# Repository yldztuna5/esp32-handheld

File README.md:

# ESP32 Handheld

3D baskı kasalı, ESP32-S3 tabanlı, kendi arayüzü ve mini uygulamaları olan bir el konsolu.

## Hedefler
- **Güvenli batarya:** Şarjda unutulunca ısınmayan, sıcakta ve soğukta şarjı kendiliğinden durduran bir güç devresi.
- **Uzun pil ömrü:** 18650 hücre ile ~10-12 saat kullanım.
- **Ekran:** 2.8", 320x240 (bütçe nedeniyle TN; PCB ileride IPS'e geçişe uygun).
- **Kompakt yapı:** Özel PCB ile kasaya düzgünce sığan bir tasarım.
- **USB-C:** Şarj ve programlama aynı porttan.
- **Kendi yazılımı:** Launcher ve farklı oyunlar/mini uygulamalar.

## Klasörler
| Klasör | İçerik |
|---|---|
| [`docs/`](docs/) | Kararlar, güç/güvenlik tasarımı, parça listeleri |
| [`firmware/`](firmware/) | ESP32-S3 yazılımı (PlatformIO) |
| [`hardware/pcb/`](hardware/pcb/) | KiCad şema ve PCB dosyaları |
| [`hardware/case/`](hardware/case/) | 3D kasa tasarımı (STEP/STL) |

## Belgeler
- [Donanım kararları](docs/hardware.md)
- [Güç ve batarya güvenliği](docs/power-safety.md)
- [Parça listesi](docs/parts.md)
- [Pin planı](docs/pinout.md)
- [Modüllü sürüm (delikli kart)](docs/module-build.md)
- [Delikli kart yerleşimi ve bağlantı tablosu](hardware/perfboard/README.md)

## Yol haritası
- [x] Gereksinimler ve temel parça kararları
- [x] Pin planı
- [x] Tasarım incelemesi (güç, pinler, ses, mekanik) ve düzeltmeler
- [ ] Prototip parçalarını sipariş et
- [ ] Breadboard: ESP32-S3 + ekran + yön tuşu + butonlar + ses
- [ ] Firmware: launcher iskeleti ve ilk uygulama
- [x] KiCad şema (kod ile üretiliyor: `hardware/pcb/gen/`)
- [ ] Modüllü sürüm: delikli kartta montaj ([plan](docs/module-build.md))
- [ ] KiCad PCB yerleşimi (v1 taslak hazır, sipariş öncesi gözden geçirilecek)
- [ ] Kasa tasarımı (PCB ölçülerine göre)
- [ ] PCB v1 sipariş (dizgi maliyeti nedeniyle ertelendi) ve güç devresi testi (bataryasız)
- [ ] Montaj ve tam sistem testi
- [ ] PCB v2 (gerekirse)

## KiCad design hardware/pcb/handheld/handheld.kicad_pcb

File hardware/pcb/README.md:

# PCB

Kart, kodla üretilir. Tek kaynak `gen/design.py` (parçalar ve bağlantılar); şema ve kart bundan çıkar.

| Dosya | İçerik |
|---|---|
| `gen/design.py` | Devre tanımı: parçalar, pinler, LCSC kodları |
| `gen/gen_sch.py` | Şemayı üretir (`handheld/handheld.kicad_sch`) |
| `gen/gen_pcb.py`, `pcb_plan.py`, `pcb_route.py` | Kart yerleşimi ve yollar (`handheld/handheld.kicad_pcb`) |
| `gen/check_netlist.py`, `gen/check_pcb.py` | Şema ve kartın `design.py` ile birebir uyduğunu denetler |
| `gen/fab.py` | Üretim dosyaları (`handheld/fab/`) |
| `handheld/handheld-schematic.pdf` | Şemanın PDF'i |
| `handheld/render-top.png`, `render-bottom.png` | Kartın ön ve arka görüntüsü |
| `handheld/fab/gerbers.zip`, `bom-jlcpcb.csv`, `cpl-jlcpcb.csv` | Fiyat teklifi ve sipariş için yüklenecek dosyalar |

Yeniden üretmek için `gen/` içinde `run.ps1` (KiCad 9 gerekir), sonra `check_pcb.py` ve `fab.py`.

## Durum (v1.1 taslak)
- 90 x 100 mm, 2 katman. Bütün SMD parçalar arka yüzde (tek yüz dizgi); ön yüzde ekran başlıkları ve butonlar.
- Ana güç yolları en az 0,6 mm (batarya hattı 1,0 mm); sadece çip pinlerine girişte 1-2 mm'lik ince boyunlar var.
- ERC: 0 hata. DRC: 0 hata, 0 bağlanmamış uç, şema ile uyumlu.
- **Sipariş öncesi yapılacaklar:**
  - JLCPCB dizgi dosyasındaki parça yönlerini (rotation) önizlemede tek tek kontrol etmek.
  - Gerber'leri bir görüntüleyicide açıp bakmak.
  - Ekran modülü gelince delik ve başlık konumlarını cetvelle doğrulamak.
  - Pinleri breadboard'da denemek.

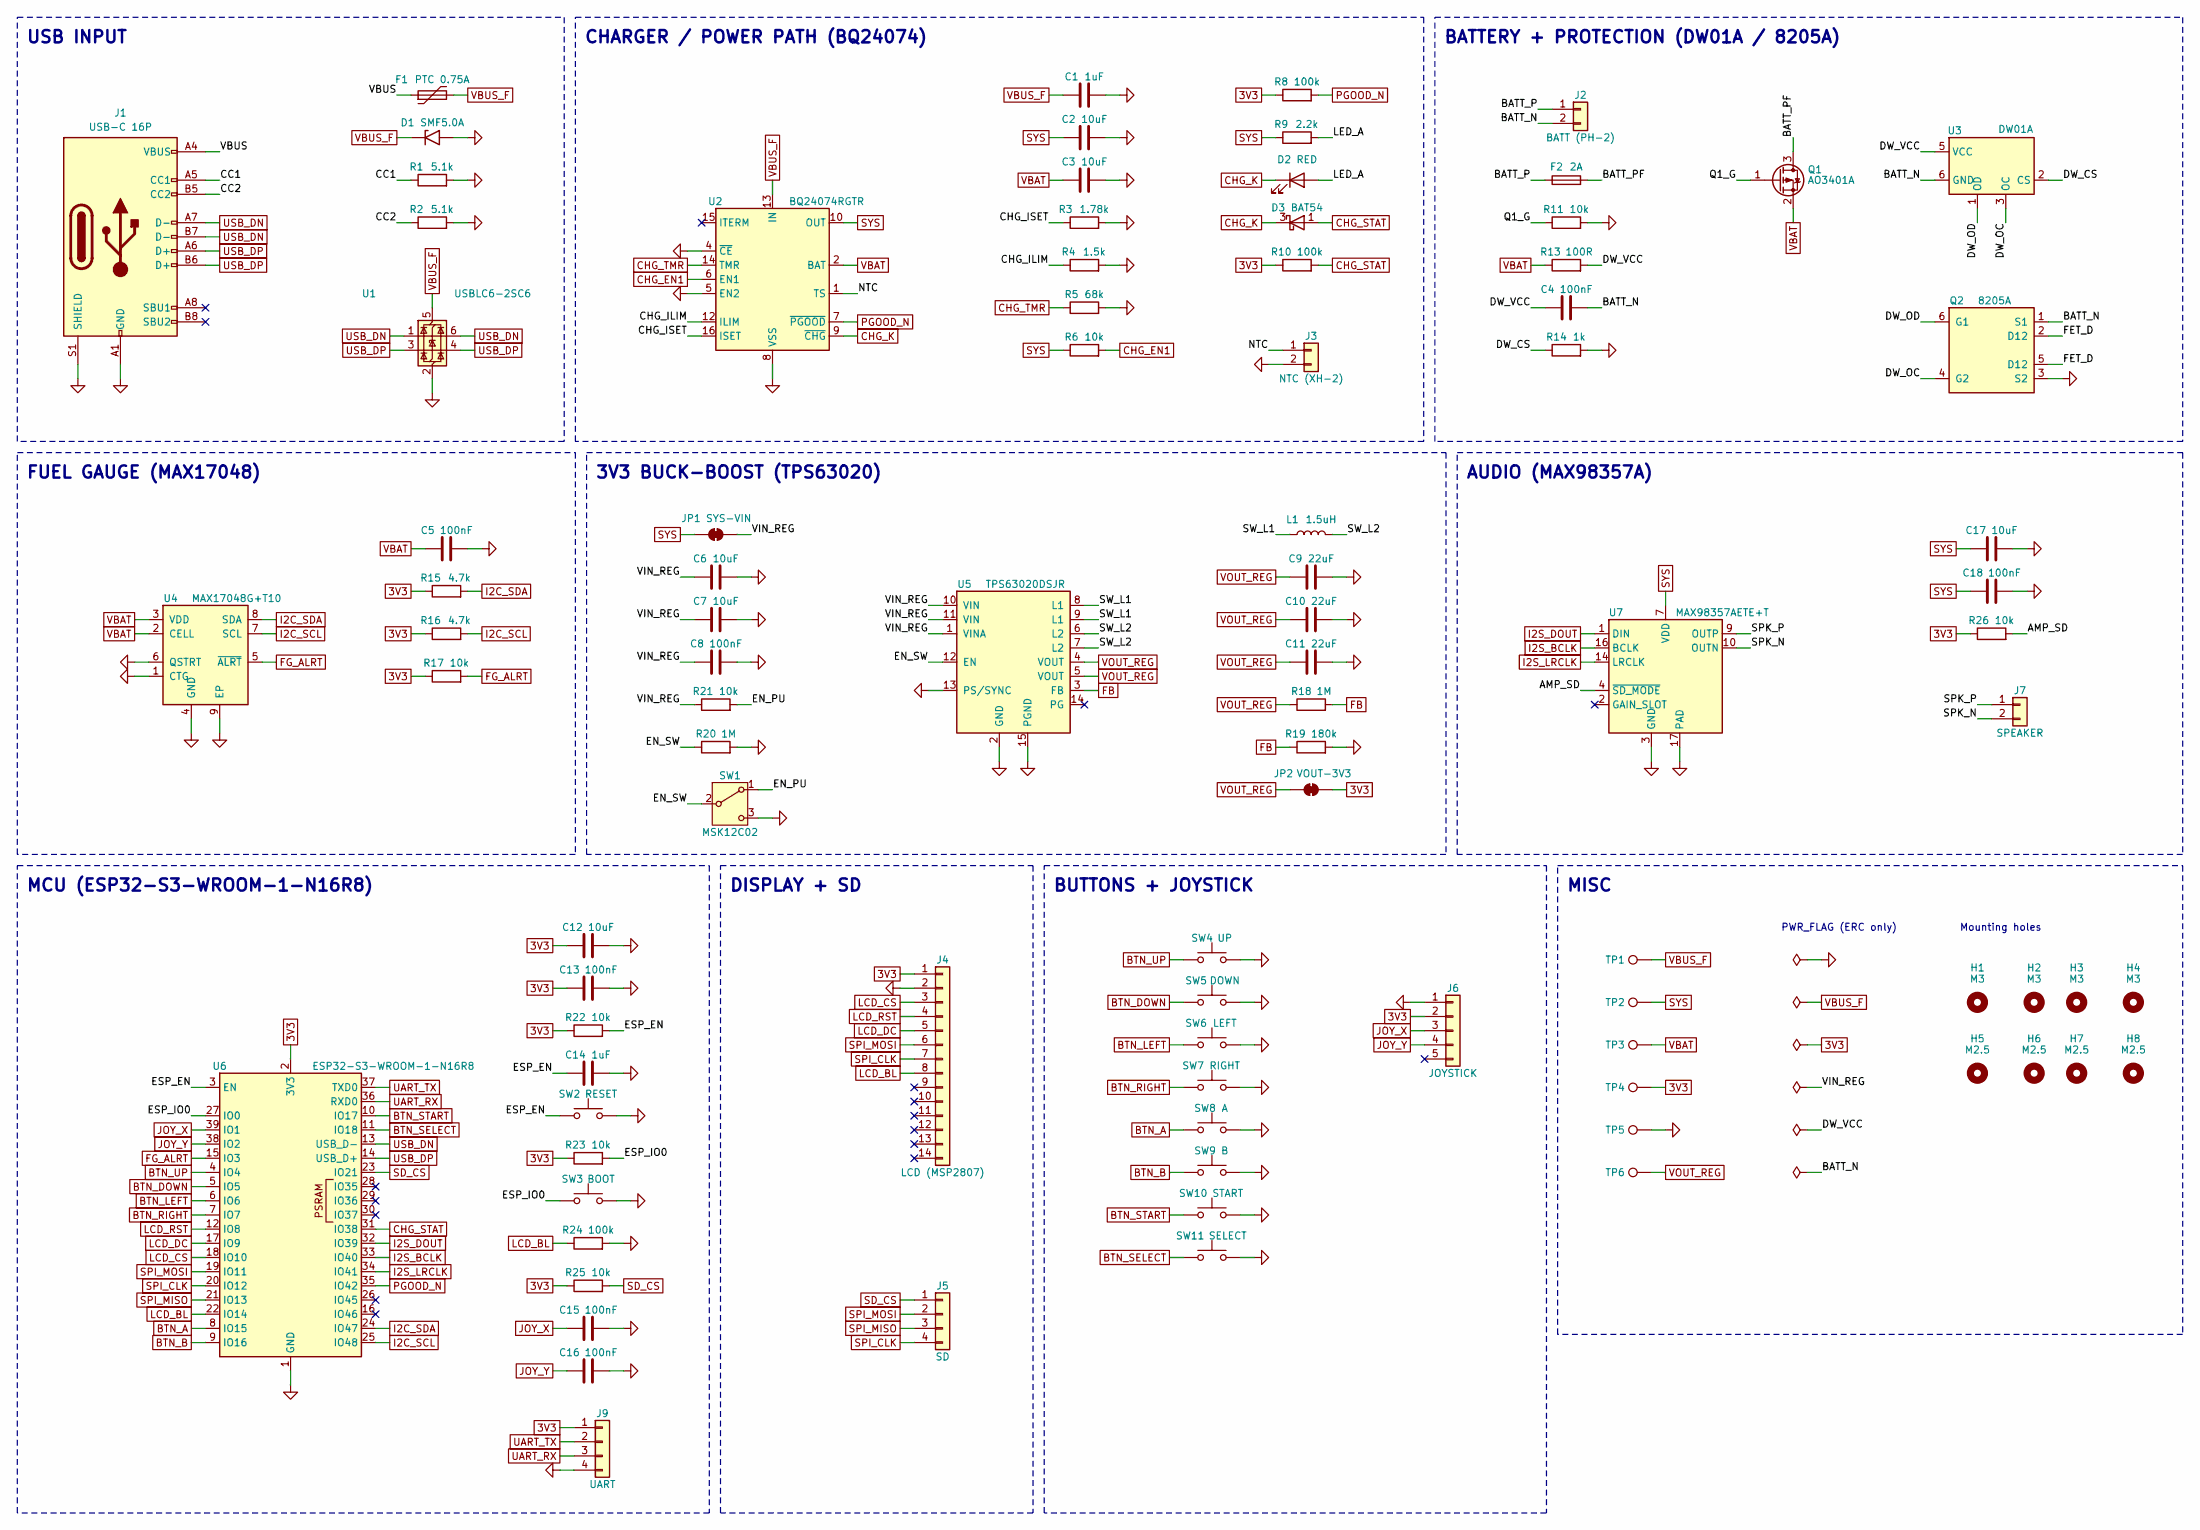
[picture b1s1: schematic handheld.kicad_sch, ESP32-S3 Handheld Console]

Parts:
C1, C14: 1uF; C_0603_1608Metric; LCSC C15849
C2, C3, C6, C7, C12, C17: 10uF; C_0603_1608Metric; LCSC C96446
C4, C5, C8, C13, C15, C16, C18: 100nF; C_0603_1608Metric; LCSC C14663
C9, C10, C11: 22uF; C_0805_2012Metric; LCSC C45783
D1: SMF5.0A; D_SOD-123F; LCSC C193402
D2: RED; LED_0603_1608Metric; LCSC C2286
D3: BAT54; SOT-23; LCSC C8590
F1: PTC 0.75A; Fuse_1206_3216Metric; LCSC C20987
F2: 2A; Fuse_1206_3216Metric; LCSC C3105
H1, H2, H3, H4: M3; MountingHole_3.2mm_M3
H5, H6, H7, H8: M2.5; MountingHole_2.7mm_M2.5
J1: USB-C 16P; USB_C_Receptacle_HRO_TYPE-C-31-M-12; LCSC C165948
J2: BATT (PH-2); JST_PH_S2B-PH-K_1x02_P2.00mm_Horizontal
J3: NTC (XH-2); JST_XH_B2B-XH-A_1x02_P2.50mm_Vertical
J4: LCD (MSP2807); PinSocket_1x14_P2.54mm_Vertical
J5: SD; PinSocket_1x04_P2.54mm_Vertical
J6: JOYSTICK; PinHeader_1x05_P2.54mm_Vertical
J7: SPEAKER; PinHeader_1x02_P2.54mm_Vertical
J9: UART; PinHeader_1x04_P2.54mm_Vertical
JP1: SYS-VIN; SolderJumper-2_P1.3mm_Bridged_RoundedPad1.0x1.5mm
JP2: VOUT-3V3; SolderJumper-2_P1.3mm_Bridged_RoundedPad1.0x1.5mm
L1: 1.5uH; L_Changjiang_FNR4020S; LCSC C167824
Q1: AO3401A; SOT-23; LCSC C15127
Q2: 8205A; SOT-23-6; LCSC C351449
R1, R2: 5.1k; R_0603_1608Metric; LCSC C23186
R3: 1.78k; R_0603_1608Metric; LCSC C13118
R4: 1.5k; R_0603_1608Metric; LCSC C22843
R5: 68k; R_0603_1608Metric; LCSC C23231
R6, R11, R17, R21, R22, R23, R25, R26: 10k; R_0603_1608Metric; LCSC C25804
R8, R10, R24: 100k; R_0603_1608Metric; LCSC C25803
R9: 2.2k; R_0603_1608Metric; LCSC C4190
R13: 100R; R_0603_1608Metric; LCSC C22775
R14: 1k; R_0603_1608Metric; LCSC C21190
R15, R16: 4.7k; R_0603_1608Metric; LCSC C23162
R18, R20: 1M; R_0603_1608Metric; LCSC C22935
R19: 180k; R_0603_1608Metric; LCSC C22827
SW1: MSK12C02; SW_SPDT_Shouhan_MSK12C02; LCSC C431540
SW2: RESET; SW_Push_1P1T_XKB_TS-1187A; LCSC C318884
SW3: BOOT; SW_Push_1P1T_XKB_TS-1187A; LCSC C318884
SW4: UP; SW_PUSH_6mm
SW5: DOWN; SW_PUSH_6mm
SW6: LEFT; SW_PUSH_6mm
SW7: RIGHT; SW_PUSH_6mm
SW8: A; SW_PUSH_6mm
SW9: B; SW_PUSH_6mm
SW10: START; SW_PUSH_6mm
SW11: SELECT; SW_PUSH_6mm
TP1: VBUS_F; TestPoint_Pad_D1.5mm
TP2: SYS; TestPoint_Pad_D1.5mm
TP3: VBAT; TestPoint_Pad_D1.5mm
TP4: 3V3; TestPoint_Pad_D1.5mm
TP5: GND; TestPoint_Pad_D1.5mm
TP6: VOUT_REG; TestPoint_Pad_D1.5mm
U1: USBLC6-2SC6; SOT-23-6; LCSC C7519
U2: BQ24074RGTR; VQFN-16-1EP_3x3mm_P0.5mm_EP1.6x1.6mm; LCSC C54313
U3: DW01A; SOT-23-6; LCSC C351410
U4: MAX17048G+T10; TDFN-8-1EP_2x2mm_P0.5mm_EP0.8x1.2mm; LCSC C2682616
U5: TPS63020DSJR; TPS63020_DSJ; LCSC C15483
U6: ESP32-S3-WROOM-1-N16R8; ESP32-S3-WROOM-1; LCSC C2913202
U7: MAX98357AETE+T; TQFN-16-1EP_3x3mm_P0.5mm_EP1.23x1.23mm; LCSC C910544

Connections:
3V3: C12.1, C13.1, J4.1, J6.2, J9.1, JP2.2 (B), R8.1, R10.1, R15.1, R16.1, R17.1, R22.1, R23.1, R25.1, R26.1, TP4.1, U6.2 (3V3)
/AMP_SD: R26.2, U7.4 (~SD_MODE)
/BATT_N: C4.2, J2.2, Q2.1 (S1), U3.6 (GND)
/BATT_P: F2.1, J2.1
/BATT_PF: F2.2, Q1.3 (D)
/CC1: J1.A5 (CC1), R1.1
/CC2: J1.B5 (CC2), R2.1
/CHG_ILIM: R4.1, U2.12 (ILIM)
/CHG_ISET: R3.1, U2.16 (ISET)
/DW_CS: R14.1, U3.2 (CS)
/DW_OC: Q2.4 (G2), U3.3 (OC)
/DW_OD: Q2.6 (G1), U3.1 (OD)
/DW_VCC: C4.1, R13.2, U3.5 (VCC)
/EN_PU: R21.2, SW1.1 (A)
/EN_SW: R20.1, SW1.2 (B), U5.12 (EN)
/ESP_EN: C14.1, R22.2, SW2.1, U6.3 (EN)
/ESP_IO0: R23.2, SW3.1, U6.27 (IO0)
/FET_D: Q2.2 (D12), Q2.5 (D12)
/LED_A: D2.2 (A), R9.2
/NTC: J3.1, U2.1 (TS)
/Q1_G: Q1.1 (G), R11.1
/SPK_N: J7.2, U7.10 (OUTN)
/SPK_P: J7.1, U7.9 (OUTP)
/SW_L1: L1.1, U5.8 (L1), U5.9 (L1)
/SW_L2: L1.2, U5.6 (L2), U5.7 (L2)
/VBUS: F1.1, J1.A4 (VBUS), J1.A9 (VBUS), J1.B4 (VBUS), J1.B9 (VBUS)
/VIN_REG: C6.1, C7.1, C8.1, JP1.2 (B), R21.1, U5.1 (VINA), U5.10 (VIN), U5.11 (VIN)
BTN_A: SW8.1, U6.8 (IO15)
BTN_B: SW9.1, U6.9 (IO16)
BTN_DOWN: SW5.1, U6.5 (IO5)
BTN_LEFT: SW6.1, U6.6 (IO6)
BTN_RIGHT: SW7.1, U6.7 (IO7)
BTN_SELECT: SW11.1, U6.11 (IO18)
BTN_START: SW10.1, U6.10 (IO17)
BTN_UP: SW4.1, U6.4 (IO4)
CHG_EN1: R6.2, U2.6 (EN1)
CHG_K: D2.1 (K), D3.3 (K), U2.9 (~CHG)
CHG_STAT: D3.1 (A), R10.2, U6.31 (IO38)
CHG_TMR: R5.1, U2.14 (TMR)
FB: R18.2, R19.1, U5.3 (FB)
FG_ALRT: R17.2, U4.5 (~ALRT), U6.15 (IO3)
GND: C1.2, C2.2, C3.2, C5.2, C6.2, C7.2, C8.2, C9.2, C10.2, C11.2, C12.2, C13.2, C14.2, C15.2, C16.2, C17.2, C18.2, D1.2 (A2), J1.A1 (GND), J1.A12 (GND), J1.B1 (GND), J1.B12 (GND), J1.S1 (SHIELD), J3.2, J4.2, J6.1, J9.4, Q2.3 (S2), R1.2, R2.2, R3.2, R4.2, R5.2, R11.2, R14.2, R19.2, R20.2, R24.2, SW1.3 (C), SW2.2, SW3.2, SW4.2, SW5.2, SW6.2, SW7.2, SW8.2, SW9.2, SW10.2, SW11.2, TP5.1, U1.2 (GND), U2.4 (~CE), U2.5 (EN2), U2.8 (VSS), U2.17 (VSS), U4.1 (CTG), U4.4 (GND), U4.6 (QSTRT), U4.9 (EP), U5.2 (GND), U5.13 (PS/SYNC), U5.15 (PGND), U6.1 (GND), U6.40 (GND), U6.41 (GND), U7.3 (GND), U7.11 (GND), U7.15 (GND), U7.17 (PAD)
I2C_SCL: R16.2, U4.7 (SCL), U6.25 (IO48)
I2C_SDA: R15.2, U4.8 (SDA), U6.24 (IO47)
I2S_BCLK: U6.33 (IO40), U7.16 (BCLK)
I2S_DOUT: U6.32 (IO39), U7.1 (DIN)
I2S_LRCLK: U6.34 (IO41), U7.14 (LRCLK)
JOY_X: C15.1, J6.3, U6.39 (IO1)
JOY_Y: C16.1, J6.4, U6.38 (IO2)
LCD_BL: J4.8, R24.1, U6.22 (IO14)
LCD_CS: J4.3, U6.18 (IO10)
LCD_DC: J4.5, U6.17 (IO9)
LCD_RST: J4.4, U6.12 (IO8)
PGOOD_N: R8.2, U2.7 (~PGOOD), U6.35 (IO42)
SD_CS: J5.1, R25.2, U6.23 (IO21)
SPI_CLK: J4.7, J5.4, U6.20 (IO12)
SPI_MISO: J5.3, U6.21 (IO13)
SPI_MOSI: J4.6, J5.2, U6.19 (IO11)
SYS: C2.1, C17.1, C18.1, JP1.1 (A), R6.1, R9.1, TP2.1, U2.10 (OUT), U2.11 (OUT), U7.7 (VDD), U7.8 (VDD)
UART_RX: J9.3, U6.36 (RXD0)
UART_TX: J9.2, U6.37 (TXD0)
USB_DN: J1.A7 (D-), J1.B7 (D-), U1.1 (I/O1), U1.6 (I/O1), U6.13 (USB_D-)
USB_DP: J1.A6 (D+), J1.B6 (D+), U1.3 (I/O2), U1.4 (I/O2), U6.14 (USB_D+)
VBAT: C3.1, C5.1, Q1.2 (S), R13.1, TP3.1, U2.2 (BAT), U2.3 (BAT), U4.2 (CELL), U4.3 (VDD)
VBUS_F: C1.1, D1.1 (A1), F1.2, TP1.1, U1.5 (VBUS), U2.13 (IN)
VOUT_REG: C9.1, C10.1, C11.1, JP2.1 (A), R18.1, TP6.1, U5.4 (VOUT), U5.5 (VOUT)

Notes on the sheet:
USB INPUT
CHARGER / POWER PATH (BQ24074)
BATTERY + PROTECTION (DW01A / 8205A)
FUEL GAUGE (MAX17048)
3V3 BUCK-BOOST (TPS63020)
AUDIO (MAX98357A)
MCU (ESP32-S3-WROOM-1-N16R8)
DISPLAY + SD
BUTTONS + JOYSTICK
MISC
PWR_FLAG (ERC only)
Mounting holes

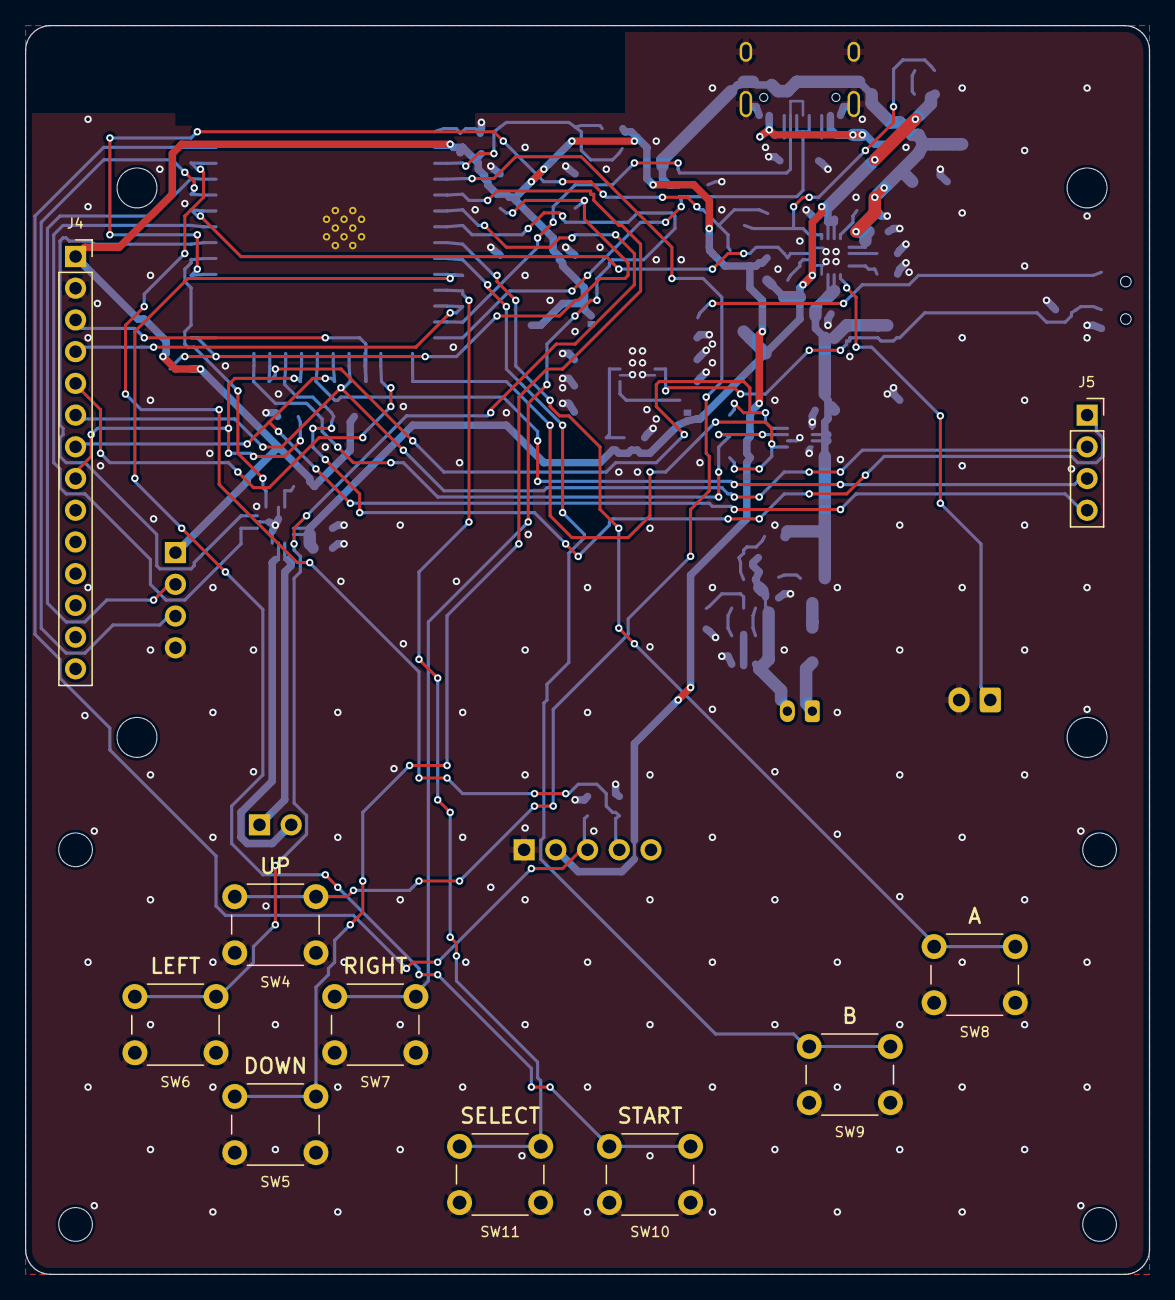
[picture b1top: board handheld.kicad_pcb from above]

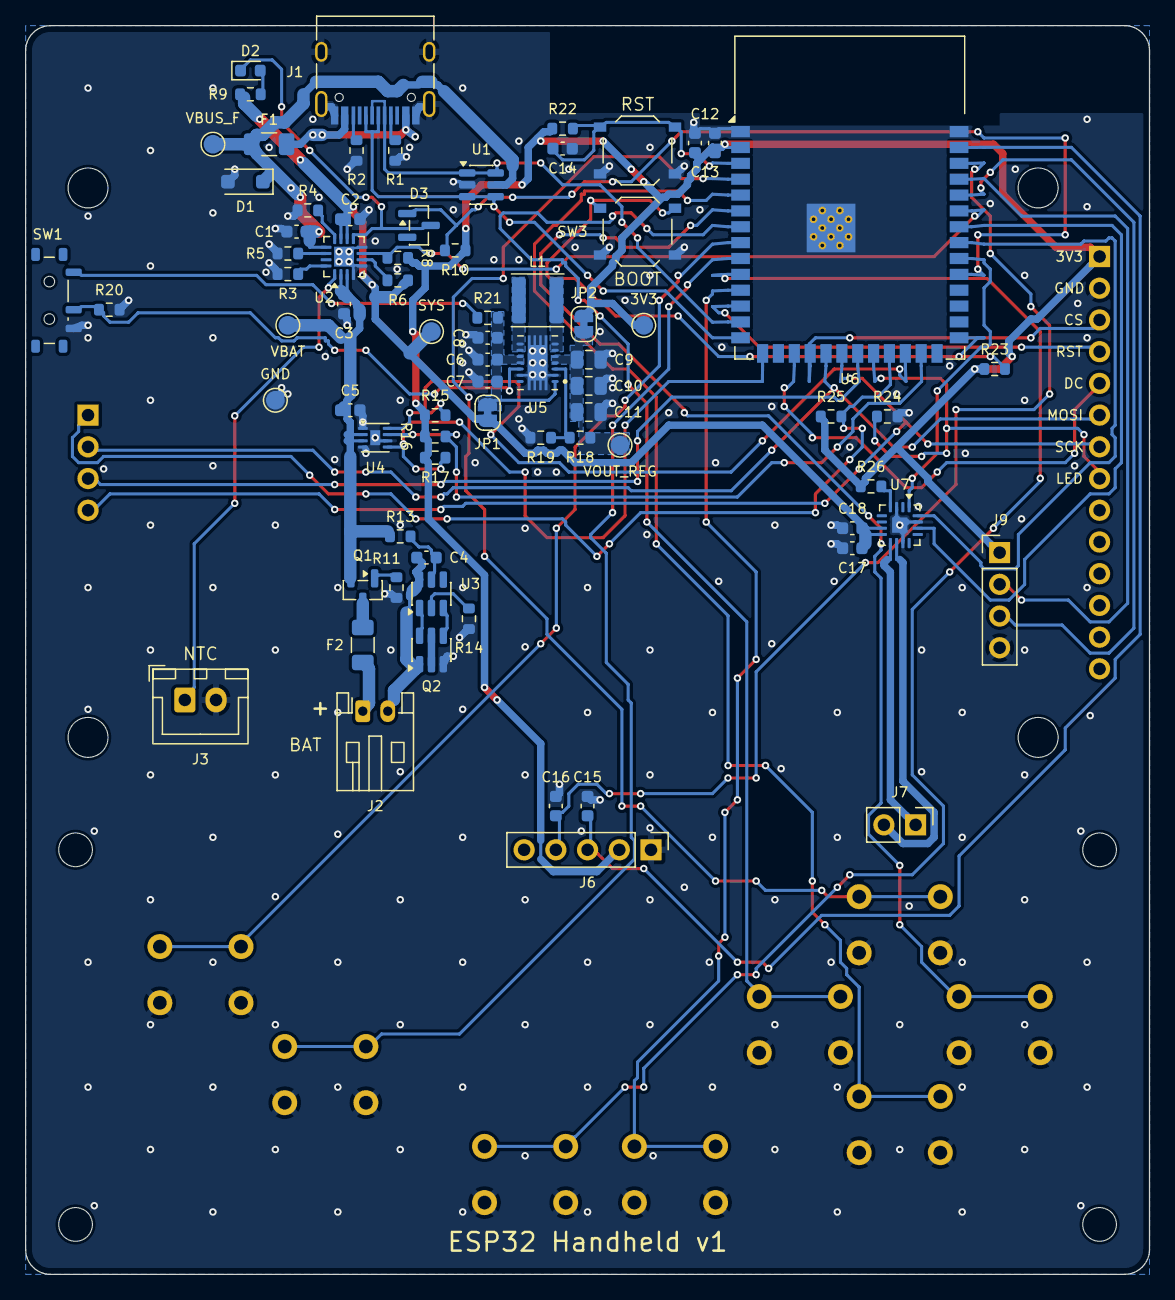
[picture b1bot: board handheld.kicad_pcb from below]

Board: 2 copper layers, 90.0 x 100.0 mm, 92 parts (74 on the bottom side), 66 nets.

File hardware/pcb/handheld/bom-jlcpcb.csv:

Comment,Designator,Footprint,LCSC Part #
1uF,"C1,C14",C_0603_1608Metric,C15849
10uF,"C2,C3,C6,C7,C12,C17",C_0603_1608Metric,C96446
100nF,"C4,C5,C8,C13,C15,C16,C18",C_0603_1608Metric,C14663
22uF,"C9,C10,C11",C_0805_2012Metric,C45783
SMF5.0A,D1,D_SOD-123F,C193402
RED,D2,LED_0603_1608Metric,C2286
BAT54,D3,SOT-23,C8590
PTC 0.75A,F1,Fuse_1206_3216Metric,C20987
2A,F2,Fuse_1206_3216Metric,C3105
USB-C 16P,J1,USB_C_Receptacle_HRO_TYPE-C-31-M-12,C165948
1.5uH,L1,L_Changjiang_FNR4020S,C167824
AO3401A,Q1,SOT-23,C15127
8205A,Q2,SOT-23-6,C351449
5.1k,"R1,R2",R_0603_1608Metric,C23186
1.78k,R3,R_0603_1608Metric,C13118
1.5k,R4,R_0603_1608Metric,C22843
68k,R5,R_0603_1608Metric,C23231
10k,"R6,R11,R17,R21,R22,R23,R25,R26",R_0603_1608Metric,C25804
100k,"R8,R10,R24",R_0603_1608Metric,C25803
2.2k,R9,R_0603_1608Metric,C4190
100R,R13,R_0603_1608Metric,C22775
1k,R14,R_0603_1608Metric,C21190
4.7k,"R15,R16",R_0603_1608Metric,C23162
1M,"R18,R20",R_0603_1608Metric,C22935
180k,R19,R_0603_1608Metric,C22827
MSK12C02,SW1,SW_SPDT_Shouhan_MSK12C02,C431540
RESET,SW2,SW_Push_1P1T_XKB_TS-1187A,C318884
BOOT,SW3,SW_Push_1P1T_XKB_TS-1187A,C318884
USBLC6-2SC6,U1,SOT-23-6,C7519
BQ24074RGTR,U2,VQFN-16-1EP_3x3mm_P0.5mm_EP1.6x1.6mm,C54313
DW01A,U3,SOT-23-6,C351410
MAX17048G+T10,U4,TDFN-8-1EP_2x2mm_P0.5mm_EP0.8x1.2mm,C2682616
TPS63020DSJR,U5,TPS63020_DSJ,C15483
ESP32-S3-WROOM-1-N16R8,U6,ESP32-S3-WROOM-1,C2913202
MAX98357AETE+T,U7,TQFN-16-1EP_3x3mm_P0.5mm_EP1.23x1.23mm,C910544

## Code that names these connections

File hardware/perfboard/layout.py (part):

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# Source-of-truth GPIO table encoded from docs/pinout.md and docs/module-build.md
# ---------------------------------------------------------------------------
PINOUT_GPIO_MAP: Dict[str, str] = {
    "GPIO10": "LCD_CS",
    "GPIO11": "SPI_MOSI",   # LCD_MOSI + SD_MOSI shared FSPI MOSI
    "GPIO12": "SPI_SCK",    # LCD_CLK + SD_CLK shared FSPI SCK
    "GPIO9": "LCD_DC",
    "GPIO8": "LCD_RST",
    "GPIO14": "LCD_BL",
    "GPIO13": "SPI_MISO",   # LCD_MISO + SD_MISO shared FSPI MISO
    "GPIO21": "SD_CS",
    "GPIO4": "DPAD_UP",
    "GPIO5": "DPAD_DOWN",
    "GPIO6": "DPAD_LEFT",
    "GPIO7": "DPAD_RIGHT",
    "GPIO15": "BTN_A",
    "GPIO16": "BTN_B",
    "GPIO17": "BTN_START",
    "GPIO18": "BTN_SELECT",
    "GPIO1": "JOY_X",
    "GPIO2": "JOY_Y",
    "GPIO39": "AUDIO_OUT",
    "GPIO3": "BAT_ADC",     # Battery voltage divider on perfboard (docs/module-build.md)
}
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    "TX(43)",   # UART0 TX debug
    "RX(44)",   # UART0 RX debug
    "GPIO42",   # PCB-only PGOOD
    "GPIO41",   # PCB-only I2S_LRCLK
    "GPIO40",   # PCB-only I2S_BCLK
    "GPIO38",   # PCB-only CHG_STAT
    "GPIO37",   # Octal PSRAM (unavailable on N16R8)
    "GPIO36",   # Octal PSRAM (unavailable on N16R8)
    "GPIO35",   # Octal PSRAM (unavailable on N16R8)
    "GPIO0",    # Strapping / onboard BOOT button
    "GPIO45",   # Strapping VDD_SPI (must NEVER be pulled high)
    "GPIO48",   # PCB-only I2C_SCL / onboard RGB LED
    "GPIO47",   # PCB-only I2C_SDA
    "GPIO20",   # USB D+
    "GPIO19",   # USB D-
}
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            description="Ekran Üst 1x4 SD Header Uçan Kablo Padleri (SD_CS, MOSI, MISO, SCK)",
            body=(9, 26, 10, 27),
            pins=[
                Pin("SD_CS", 9, 26, nc=False),
                Pin("SD_MOSI", 10, 26, nc=False),
                Pin("SD_MISO", 9, 27, nc=False),
                Pin("SD_SCK", 10, 27, nc=False),
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    lines.append("")
    lines.append("| Ekran Üst SD Pini | Hat Adı (Net) | `ARKA` Kart Lehim Padi (`PAD_SD`) | ESP32 Pini | Ek Eleman / Not |")
    lines.append("|---|---|---|---|---|")
    lines.append("| `SD_CS` | `SD_CS` | `PAD_SD.SD_CS` @ ARKA (9,26) | `GPIO21` (`J3_18_21` @ 10,19) | `R_SD` (10k pull-up -> `3V3`) |")
    lines.append("| `SD_MOSI` | `SPI_MOSI` | `PAD_SD.SD_MOSI` @ ARKA (10,26) | `GPIO11` (`J1_17_11` @ 1,18) | `LCD_MOSI` ile ortak SPI hattı |")
    lines.append("| `SD_MISO` | `SPI_MISO` | `PAD_SD.SD_MISO` @ ARKA (9,27) | `GPIO13` (`J1_19_13` @ 1,20) | `LCD_MISO` ile ortak SPI hattı |")
    lines.append("| `SD_SCK` | `SPI_SCK` | `PAD_SD.SD_SCK` @ ARKA (10,27) | `GPIO12` (`J1_18_12` @ 1,19) | `LCD_SCK` ile ortak SPI hattı |")
    lines.append("")

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
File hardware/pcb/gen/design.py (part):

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_part("F1", "PTC 0.75A", "Device:Polyfuse", "Fuse:Fuse_1206_3216Metric", "C20987",
      {1: "VBUS", 2: "VBUS_F"}, G, desc="SMD1206P075TF 0.75A hold 6V")
_part("D1", "SMF5.0A", "Diode:SMF5V0A", "Diode_SMD:D_SOD-123F", "C193402",
      {1: "VBUS_F", 2: "GND"}, G, desc="TVS 5V unidirectional, pin 1 = cathode")
_part("U1", "USBLC6-2SC6", "Power_Protection:USBLC6-2SC6", "Package_TO_SOT_SMD:SOT-23-6",
      "C7519", {1: "USB_DN", 6: "USB_DN", 3: "USB_DP", 4: "USB_DP", 5: "VBUS_F", 2: "GND"}, G)

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_r("R8", "100k", "3V3", "PGOOD_N", G)
_r("R9", "2.2k", "SYS", "LED_A", G)
_part("D2", "RED", "Device:LED", "LED_SMD:LED_0603_1608Metric", "C2286",
      {1: "CHG_K", 2: "LED_A"}, G, desc="KT-0603R red LED, pin 1 = cathode")
_part("D3", "BAT54", "handheld:BAT54", "Package_TO_SOT_SMD:SOT-23", "C8590",
      {1: "CHG_STAT", 2: None, 3: "CHG_K"}, G, desc="single Schottky SOT-23: 1 A, 2 NC, 3 K")
_r("R10", "100k", "3V3", "CHG_STAT", G)
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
